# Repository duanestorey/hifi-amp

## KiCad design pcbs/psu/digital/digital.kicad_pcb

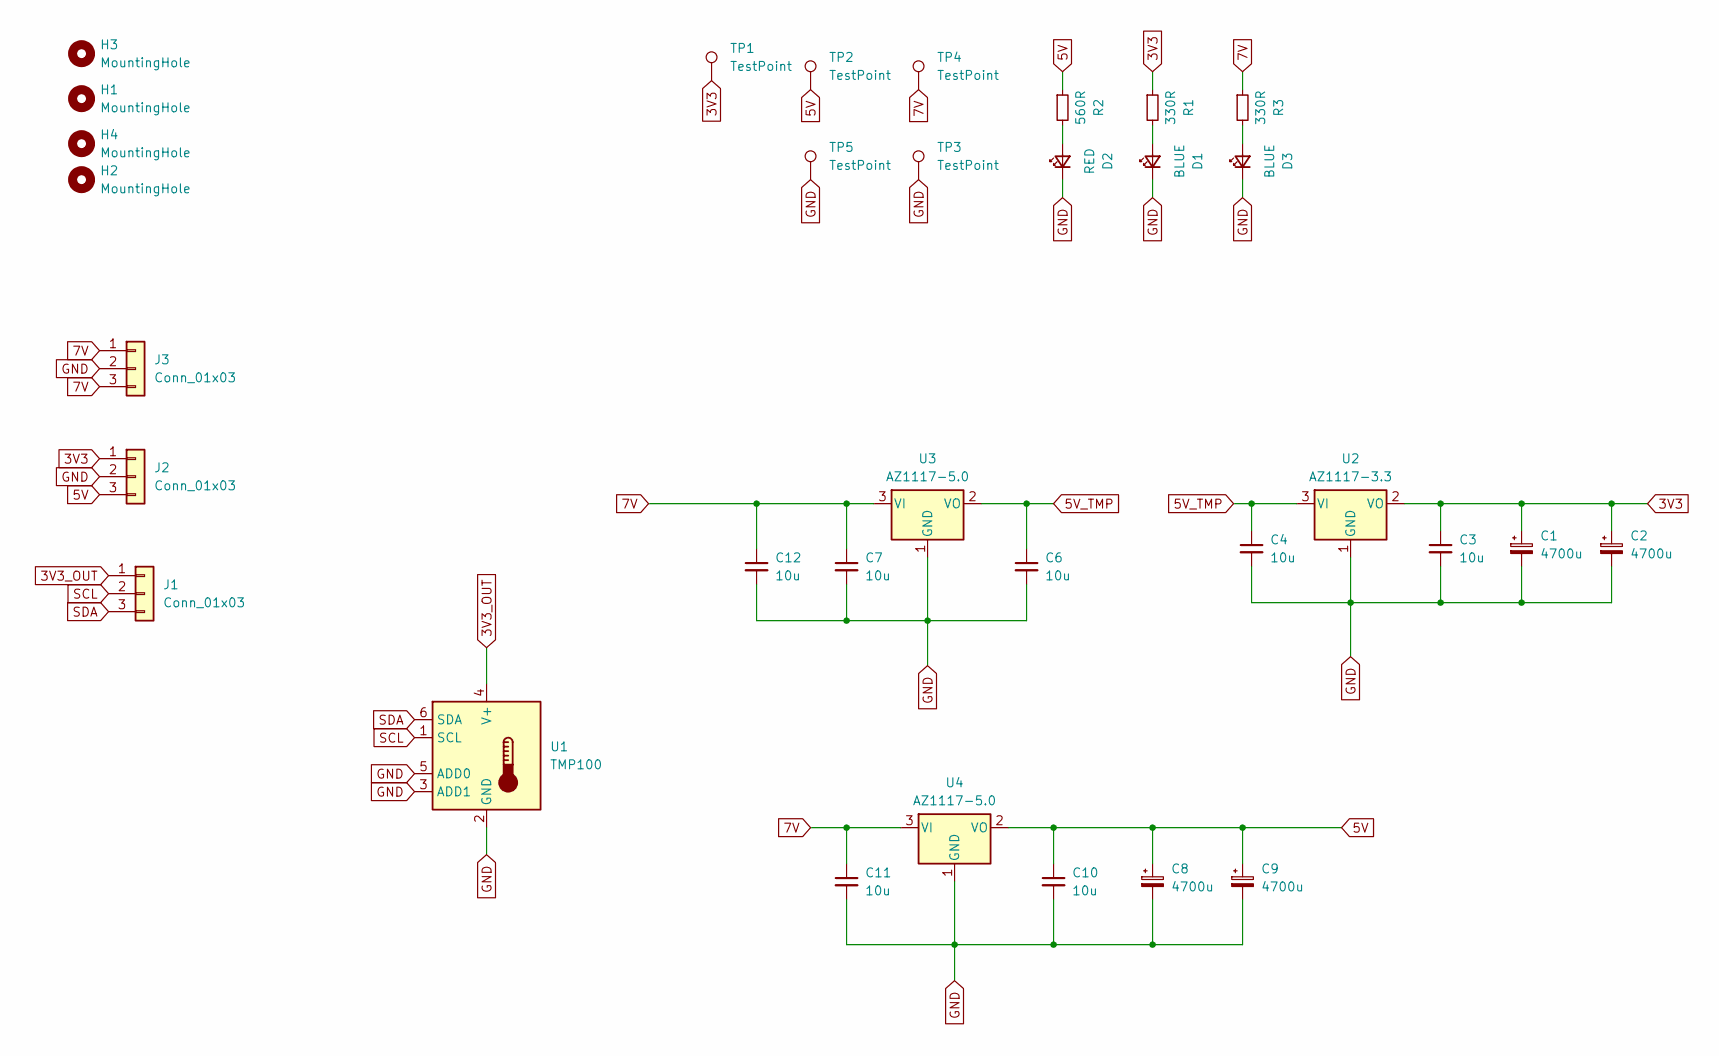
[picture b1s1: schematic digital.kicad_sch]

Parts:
C1, C2, C8, C9: 4700u; CP_Radial_D16.0mm_P7.50mm
C3, C4, C6, C7, C10, C11, C12: 10u; C_1206_3216Metric_Pad1.33x1.80mm_HandSolder
D1, D3: BLUE; LED_0805_2012Metric_Pad1.15x1.40mm_HandSolder
D2: RED; LED_0805_2012Metric_Pad1.15x1.40mm_HandSolder
H1, H2, H3, H4: MountingHole; MountingHole_3.2mm_M3_DIN965_Pad_TopBottom
J1: Conn_01x03; JST_PH_B3B-PH-K_1x03_P2.00mm_Vertical
J2, J3: Conn_01x03; JST_VH_B3P-VH-B_1x03_P3.96mm_Vertical
R1, R3: 330R; R_0805_2012Metric_Pad1.20x1.40mm_HandSolder
R2: 560R; R_0805_2012Metric_Pad1.20x1.40mm_HandSolder
TP1, TP2, TP3, TP4, TP5: TestPoint; TestPoint_THTPad_2.5x2.5mm_Drill1.2mm
U1: TMP100; SOT-23-6
U2: AZ1117-3.3; SOT-223
U3, U4: AZ1117-5.0; SOT-223

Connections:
3V3: C1.1, C2.1, C3.1, J2.1, R1.1, TP1.1, U2.2 (VO)
3V3_OUT: J1.1, U1.4 (V+)
5V: C8.1, C9.1, C10.1, J2.3, R2.1, TP2.1, U4.2 (VO)
5V_TMP: C4.1, C6.1, U2.3 (VI), U3.2 (VO)
7V: C7.1, C11.1, C12.1, J3.1, J3.3, R3.1, TP4.1, U3.3 (VI), U4.3 (VI)
GND: C1.2, C2.2, C3.2, C4.2, C6.2, C7.2, C8.2, C9.2, C10.2, C11.2, C12.2, D1.1 (K), D2.1 (K), D3.1 (K), J2.2, J3.2, TP3.1, TP5.1, U1.2 (GND), U1.3 (ADD1), U1.5 (ADD0), U2.1 (GND), U3.1 (GND), U4.1 (GND)
unnamed: D1.2 (A), R1.2
unnamed: D2.2 (A), R2.2
unnamed: D3.2 (A), R3.2
SCL: J1.2, U1.1 (SCL)
SDA: J1.3, U1.6 (SDA)

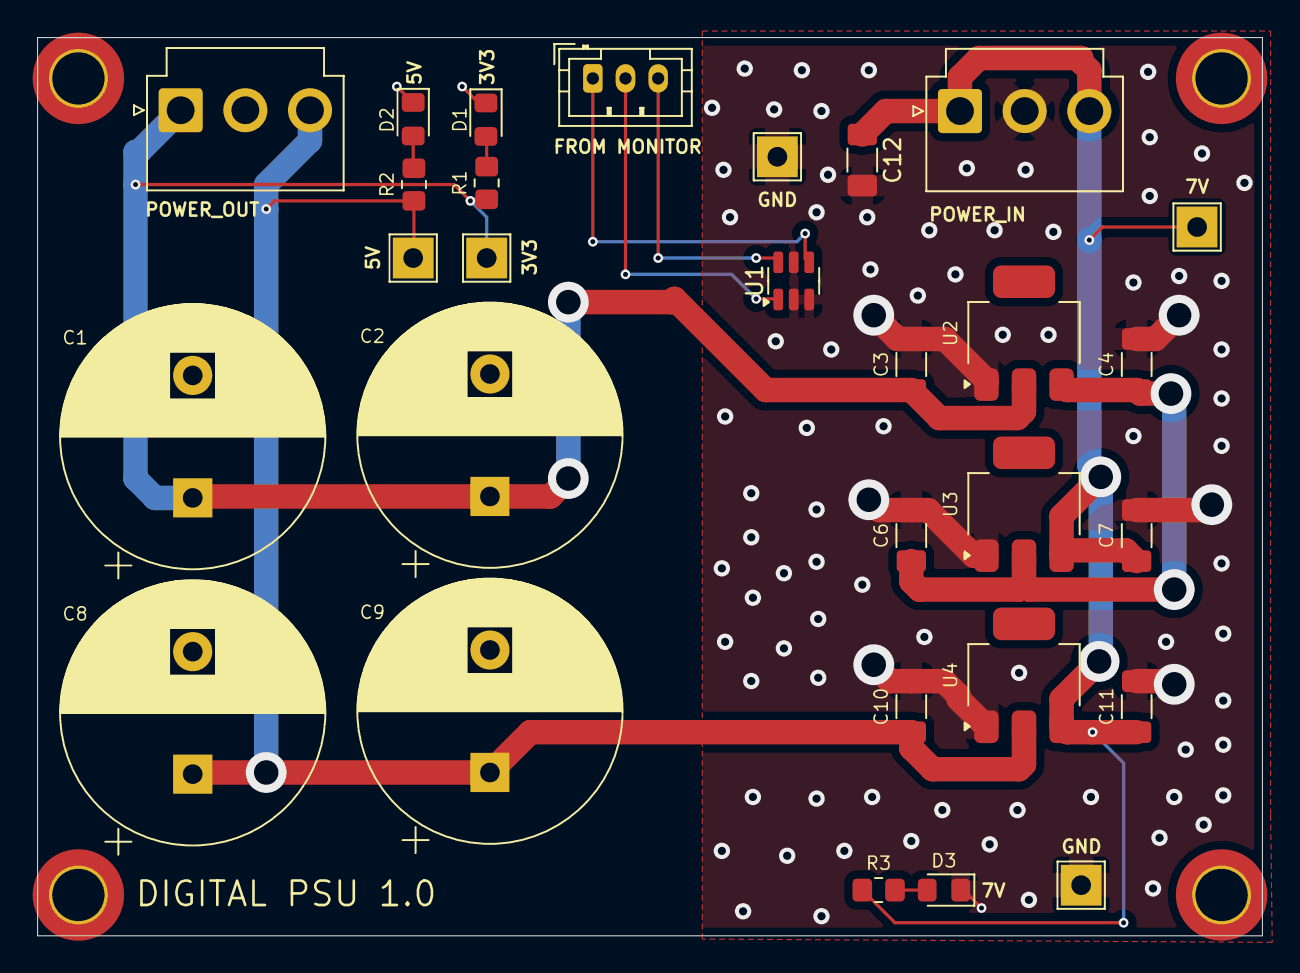
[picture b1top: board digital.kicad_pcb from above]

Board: 2 copper layers, 75.0 x 55.0 mm, 33 parts (0 on the bottom side), 11 nets.

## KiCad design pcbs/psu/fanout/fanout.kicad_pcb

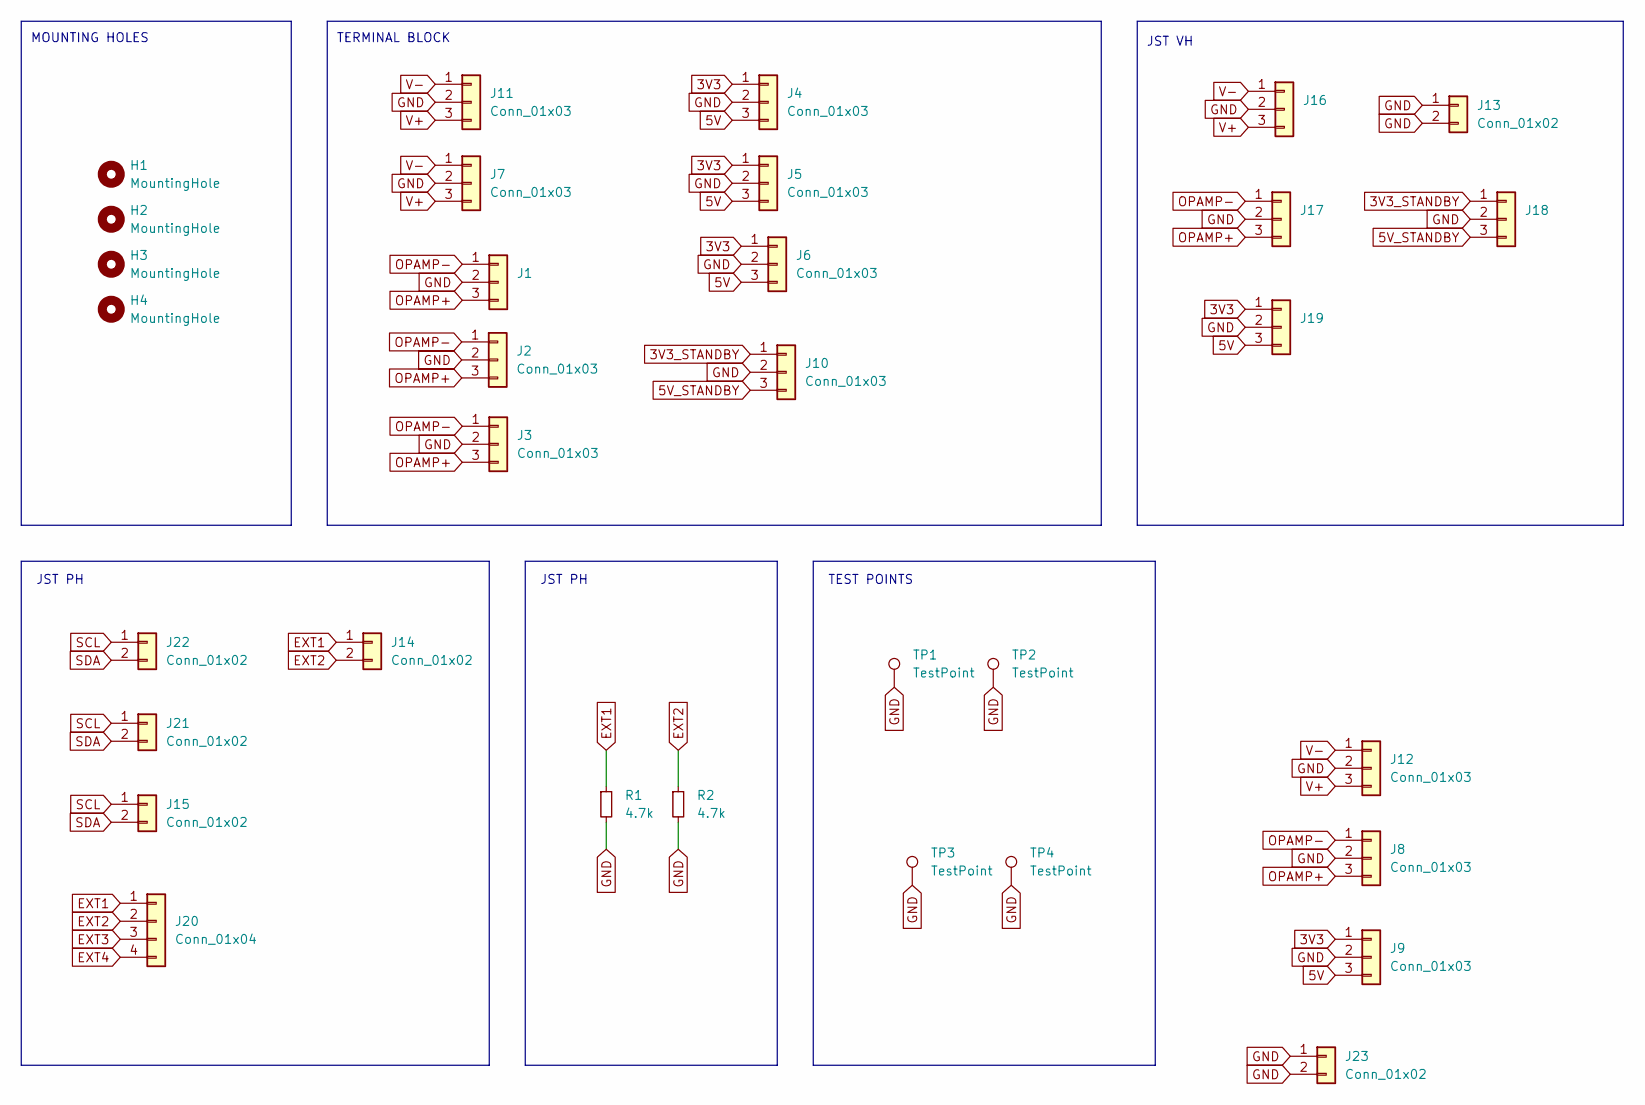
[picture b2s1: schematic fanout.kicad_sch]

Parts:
H1, H2, H3, H4: MountingHole; MountingHole_3.2mm_M3_DIN965_Pad_TopBottom
J1, J2, J3, J4, J5, J6, J7, J10, J11: Conn_01x03; TerminalBlock_Phoenix_PT-1,5-3-3.5-H_1x03_P3.50mm_Horizontal
J8, J9, J12: Conn_01x03; JST_PH_B3B-PH-K_1x03_P2.00mm_Vertical
J13: Conn_01x02; JST_VH_B2P-VH-B_1x02_P3.96mm_Vertical
J14, J15, J21, J22: Conn_01x02; JST_PH_B2B-PH-K_1x02_P2.00mm_Vertical
J16, J17, J18, J19: Conn_01x03; JST_VH_B3P-VH-B_1x03_P3.96mm_Vertical
J20: Conn_01x04; JST_PH_B4B-PH-K_1x04_P2.00mm_Vertical
J23: Conn_01x02; PinHeader_1x02_P2.54mm_Vertical
R1, R2: 4.7k; R_0805_2012Metric_Pad1.20x1.40mm_HandSolder
TP1, TP2, TP3, TP4: TestPoint; TestPoint_THTPad_2.5x2.5mm_Drill1.2mm

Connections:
3V3: J4.1, J5.1, J6.1, J9.1, J19.1
3V3_STANDBY: J10.1, J18.1
5V: J4.3, J5.3, J6.3, J9.3, J19.3
5V_STANDBY: J10.3, J18.3
EXT1: J14.1, J20.1, R1.1
EXT2: J14.2, J20.2, R2.1
EXT3: J20.3
EXT4: J20.4
GND: J1.2, J2.2, J3.2, J4.2, J5.2, J6.2, J7.2, J8.2, J9.2, J10.2, J11.2, J12.2, J13.1, J13.2, J16.2, J17.2, J18.2, J19.2, J23.1, J23.2, R1.2, R2.2, TP1.1, TP2.1, TP3.1, TP4.1
OPAMP+: J1.3, J2.3, J3.3, J8.3, J17.3
OPAMP-: J1.1, J2.1, J3.1, J8.1, J17.1
SCL: J15.1, J21.1, J22.1
SDA: J15.2, J21.2, J22.2
V+: J7.3, J11.3, J12.3, J16.3
V-: J7.1, J11.1, J12.1, J16.1

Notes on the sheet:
TEST POINTS
JST VH
MOUNTING HOLES
JST PH
TERMINAL BLOCK

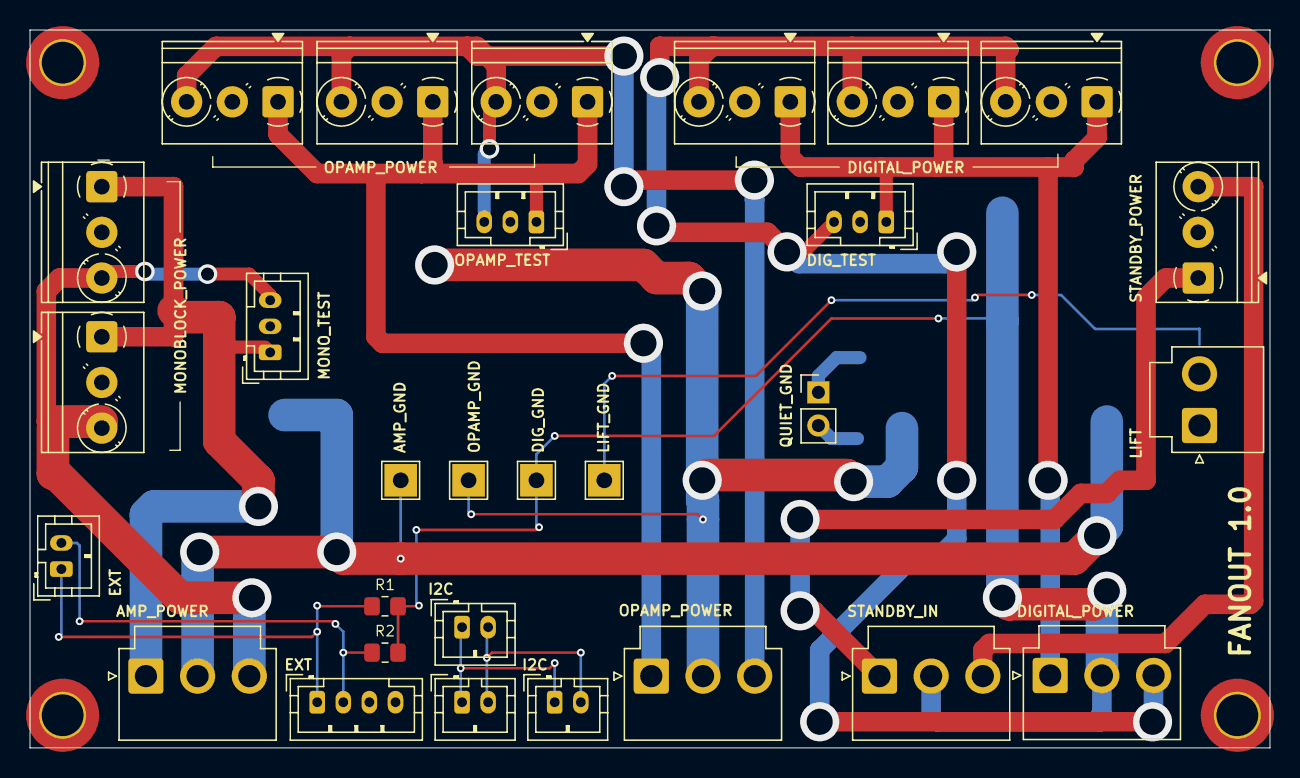
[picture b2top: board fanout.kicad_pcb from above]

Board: 2 copper layers, 95.0 x 55.0 mm, 33 parts (0 on the bottom side), 13 nets.

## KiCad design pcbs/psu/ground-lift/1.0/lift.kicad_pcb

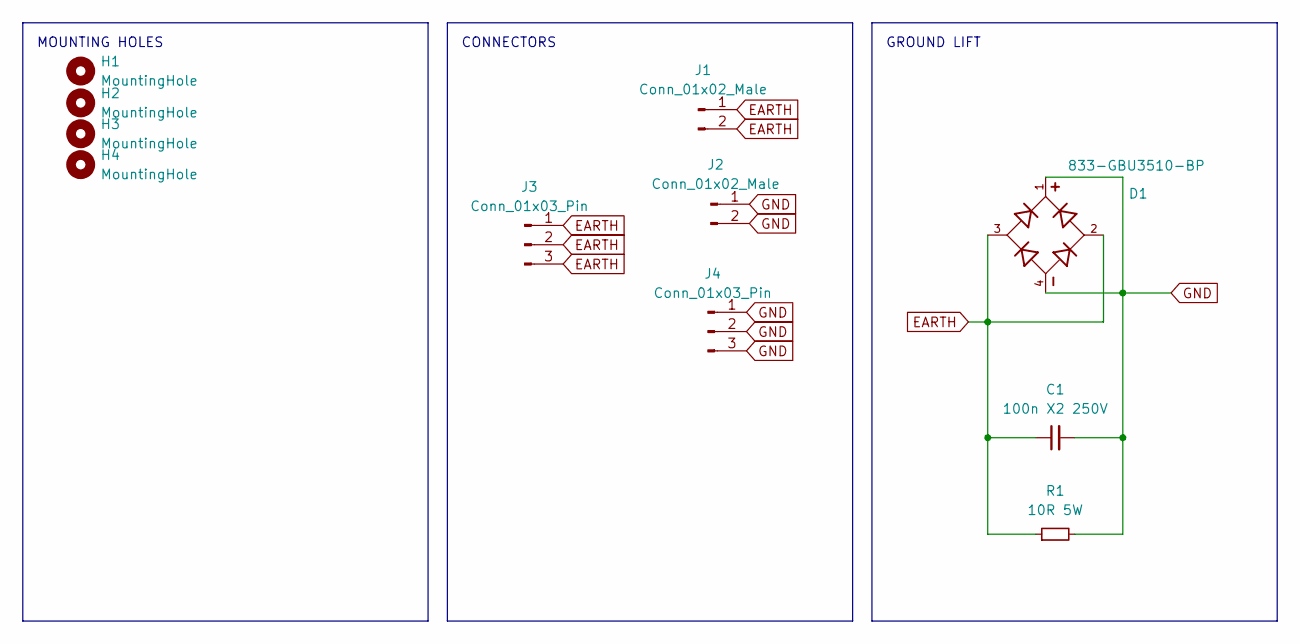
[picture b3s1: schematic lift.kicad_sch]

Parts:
C1: 100n X2 250V; C_Rect_L18.0mm_W5.0mm_P15.00mm_FKS3_FKP3; Mouser 871-B32922X2104K000
D1: 833-GBU3510-BP; Diode_Bridge_Vishay_GBU; Mouser 833-GBU3510-BP
H1, H2, H3, H4: MountingHole; MountingHole_3.2mm_M3_DIN965_Pad_TopOnly
J1, J2: Conn_01x02_Male; JST_VH_B2P-VH-B_1x02_P3.96mm_Vertical
J3, J4: Conn_01x03_Pin; TerminalBlock_Phoenix_PT-1,5-3-5.0-H_1x03_P5.00mm_Horizontal
R1: 10R 5W; R_Axial_DIN0617_L17.0mm_D6.0mm_P25.40mm_Horizontal; Mouser 594-AC05W10R00J

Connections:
EARTH: C1.1, D1.2, D1.3, J1.1, J1.2, J3.1, J3.2, J3.3, R1.1
GND: C1.2, D1.1, D1.4, J2.1, J2.2, J4.1, J4.2, J4.3, R1.2

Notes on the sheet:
CONNECTORS
GROUND LIFT
MOUNTING HOLES

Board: 2 copper layers, 11 parts (0 on the bottom side), 2 nets, no tracks yet.

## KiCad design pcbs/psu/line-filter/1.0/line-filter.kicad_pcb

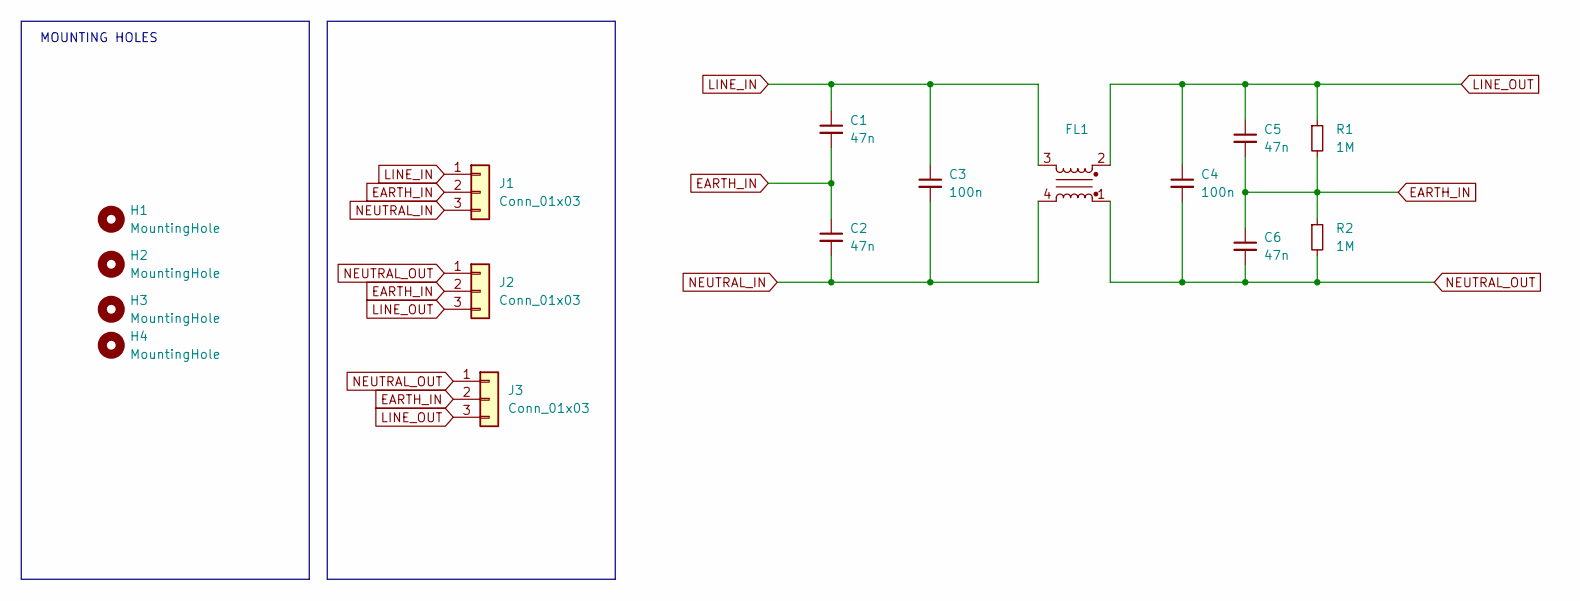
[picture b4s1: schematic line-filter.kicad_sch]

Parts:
C1, C2, C5, C6: 47n; C_Rect_L18.0mm_W7.0mm_P15.00mm_FKS3_FKP3
C3, C4: 100n; C_Rect_L18.0mm_W5.0mm_P15.00mm_FKS3_FKP3
FL1: Choke_CommonMode_PulseElectronics_PH9455x356NL; SSR21NV-M
H1, H2, H3, H4: MountingHole; MountingHole_3.2mm_M3_DIN965_Pad_TopBottom
J1, J2, J3: Conn_01x03; TerminalBlock_Phoenix_MKDS-1,5-3_1x03_P5.00mm_Horizontal
R1, R2: 1M; R_1206_3216Metric_Pad1.30x1.75mm_HandSolder

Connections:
EARTH_IN: C1.2, C2.1, C5.2, C6.1, J1.2, J2.2, J3.2, R1.2, R2.1
LINE_IN: C1.1, C3.1, FL1.3, J1.1
LINE_OUT: C4.1, C5.1, FL1.2, J2.3, J3.3, R1.1
NEUTRAL_IN: C2.2, C3.2, FL1.4, J1.3
NEUTRAL_OUT: C4.2, C6.2, FL1.1, J2.1, J3.1, R2.2

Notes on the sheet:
MOUNTING HOLES

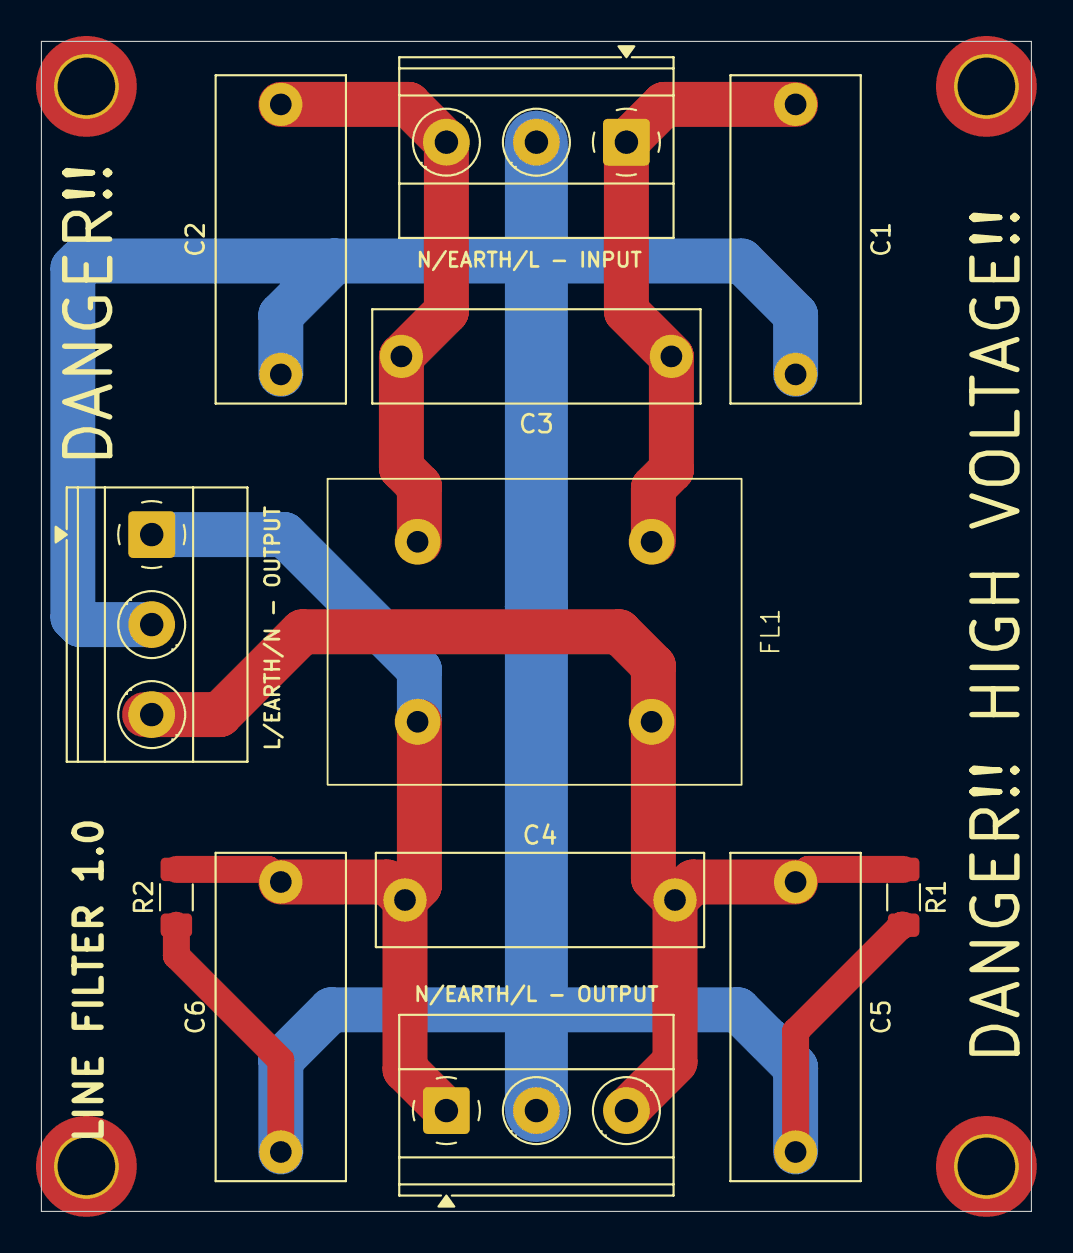
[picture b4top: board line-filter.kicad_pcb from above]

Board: 2 copper layers, 55.0 x 65.0 mm, 16 parts (0 on the bottom side), 5 nets.

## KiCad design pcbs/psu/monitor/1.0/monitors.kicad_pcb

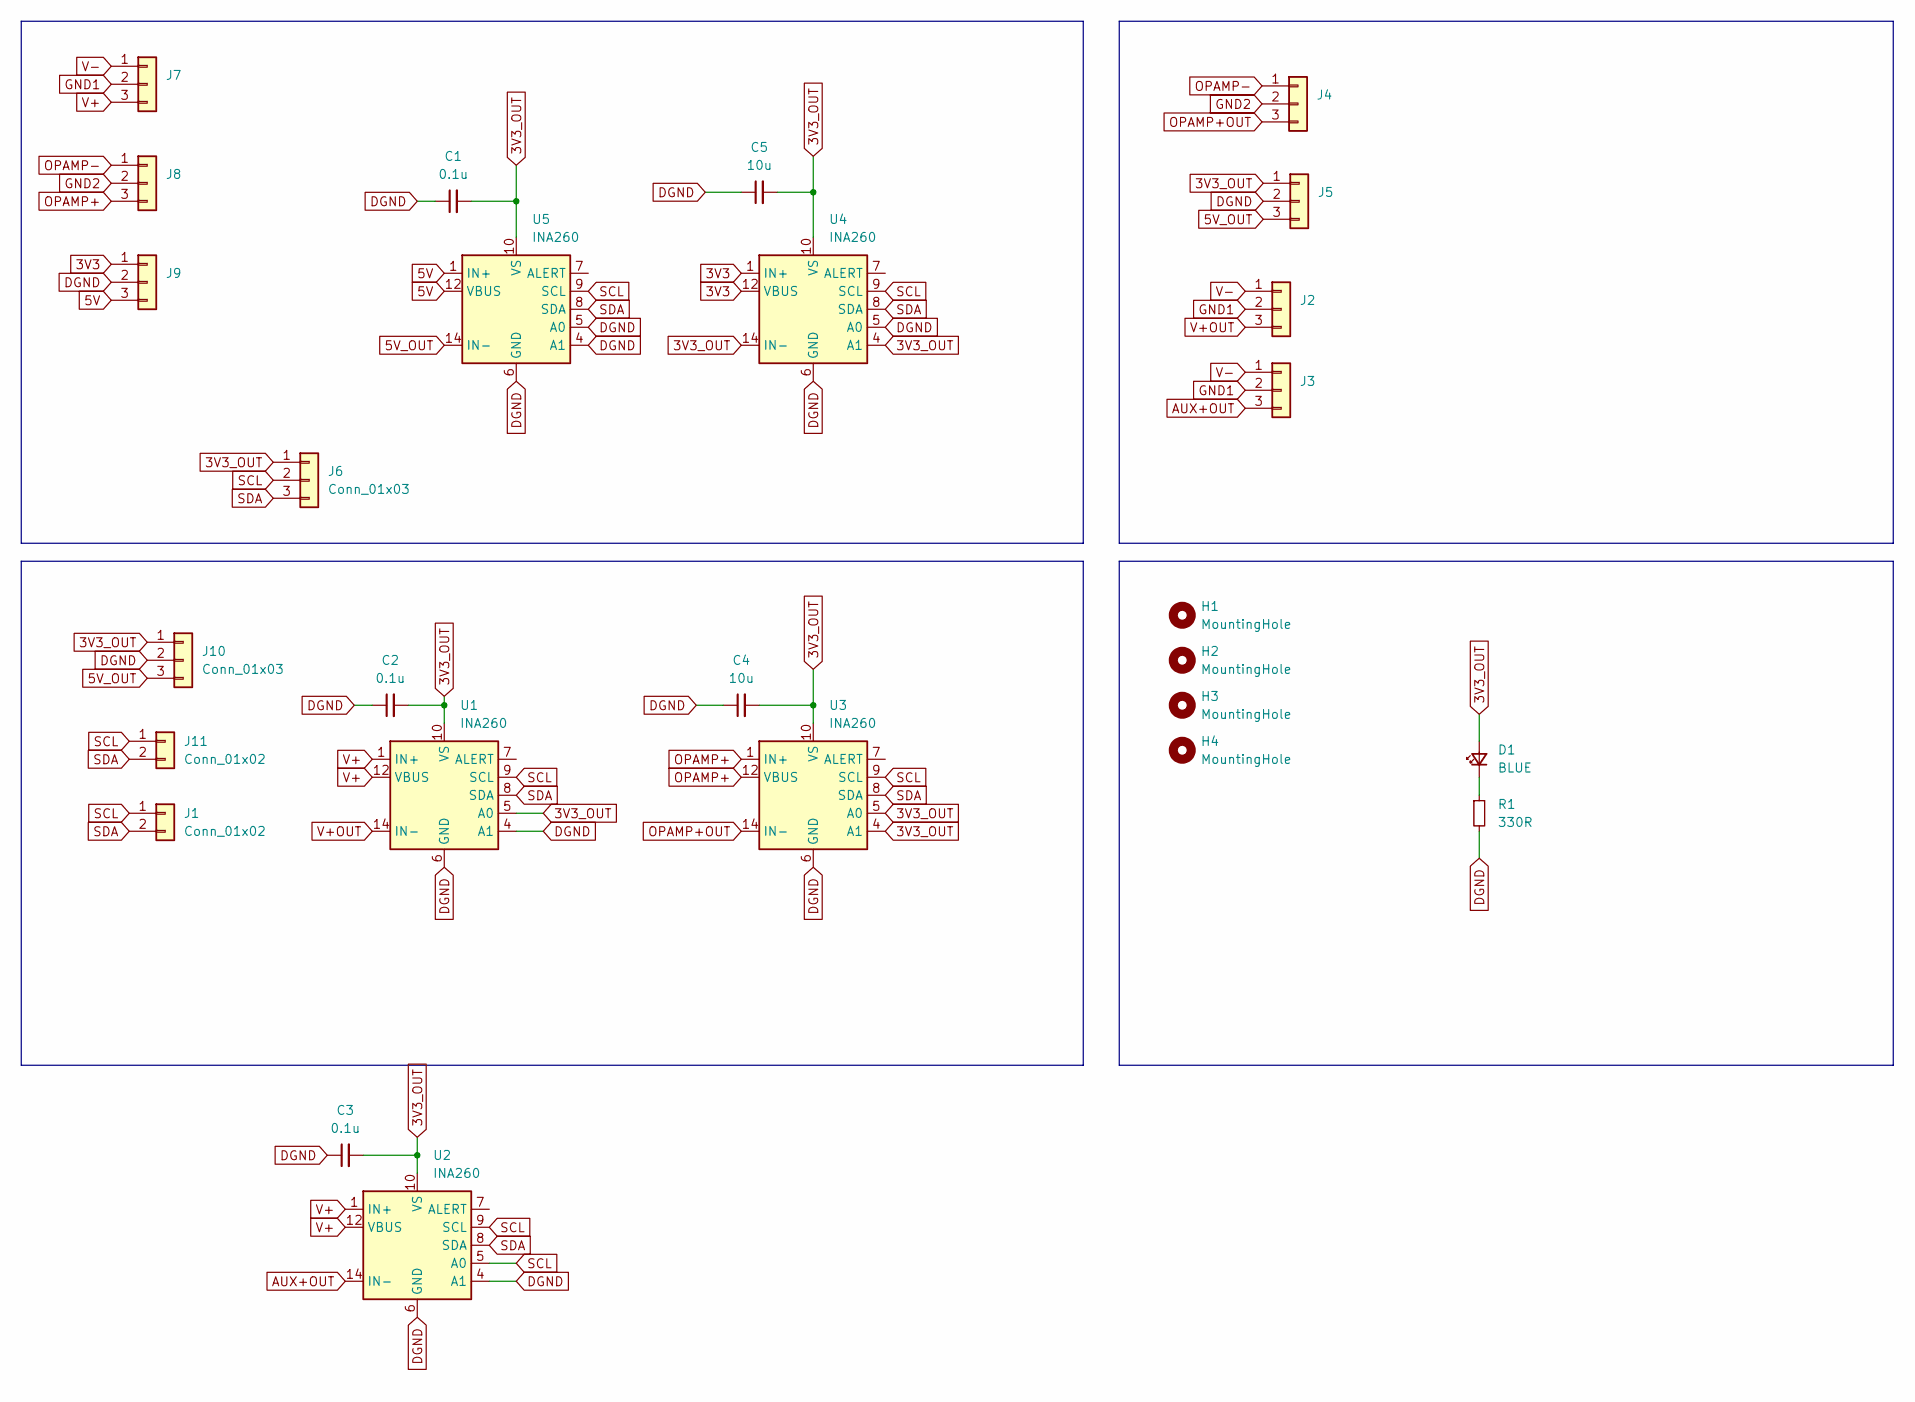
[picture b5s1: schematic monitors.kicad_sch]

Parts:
C1, C2, C3: 0.1u; C_0805_2012Metric_Pad1.18x1.45mm_HandSolder
C4, C5: 10u; C_1206_3216Metric_Pad1.33x1.80mm_HandSolder
D1: BLUE; LED_0805_2012Metric_Pad1.15x1.40mm_HandSolder
H1, H2, H3, H4: MountingHole; MountingHole_3.2mm_M3_DIN965_Pad_TopBottom
J1, J11: Conn_01x02; JST_PH_B2B-PH-K_1x02_P2.00mm_Vertical
J2, J3, J4, J5, J7, J8, J9: Conn_01x03; JST_VH_B3P-VH-B_1x03_P3.96mm_Vertical
J6, J10: Conn_01x03; JST_PH_B3B-PH-K_1x03_P2.00mm_Vertical
R1: 330R; R_0805_2012Metric_Pad1.20x1.40mm_HandSolder
U1, U2, U3, U4, U5: INA260; TSSOP-16_4.4x5mm_P0.65mm

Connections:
3V3: J9.1, U4.1 (IN+), U4.2 (IN+), U4.3 (IN+), U4.12 (VBUS)
3V3_OUT: C1.2, C2.2, C3.2, C4.2, C5.2, D1.2 (A), J5.1, J6.1, J10.1, U1.5 (A0), U1.10 (VS), U2.10 (VS), U3.4 (A1), U3.5 (A0), U3.10 (VS), U4.4 (A1), U4.10 (VS), U4.14 (IN-), U4.15 (IN-), U4.16 (IN-), U5.10 (VS)
5V: J9.3, U5.1 (IN+), U5.2 (IN+), U5.3 (IN+), U5.12 (VBUS)
5V_OUT: J5.3, J10.3, U5.14 (IN-), U5.15 (IN-), U5.16 (IN-)
AUX+OUT: J3.3, U2.14 (IN-), U2.15 (IN-), U2.16 (IN-)
DGND: C1.1, C2.1, C3.1, C4.1, C5.1, J5.2, J9.2, J10.2, R1.2, U1.4 (A1), U1.6 (GND), U1.11 (GND), U2.4 (A1), U2.6 (GND), U2.11 (GND), U3.6 (GND), U3.11 (GND), U4.5 (A0), U4.6 (GND), U4.11 (GND), U5.4 (A1), U5.5 (A0), U5.6 (GND), U5.11 (GND)
GND1: J2.2, J3.2, J7.2
GND2: J4.2, J8.2
unnamed: D1.1 (K), R1.1
OPAMP+: J8.3, U3.1 (IN+), U3.2 (IN+), U3.3 (IN+), U3.12 (VBUS)
OPAMP+OUT: J4.3, U3.14 (IN-), U3.15 (IN-), U3.16 (IN-)
OPAMP-: J4.1, J8.1
SCL: J1.1, J6.2, J11.1, U1.9 (SCL), U2.5 (A0), U2.9 (SCL), U3.9 (SCL), U4.9 (SCL), U5.9 (SCL)
SDA: J1.2, J6.3, J11.2, U1.8 (SDA), U2.8 (SDA), U3.8 (SDA), U4.8 (SDA), U5.8 (SDA)
V+: J7.3, U1.1 (IN+), U1.2 (IN+), U1.3 (IN+), U1.12 (VBUS), U2.1 (IN+), U2.2 (IN+), U2.3 (IN+), U2.12 (VBUS)
V+OUT: J2.3, U1.14 (IN-), U1.15 (IN-), U1.16 (IN-)
V-: J2.1, J3.1, J7.1

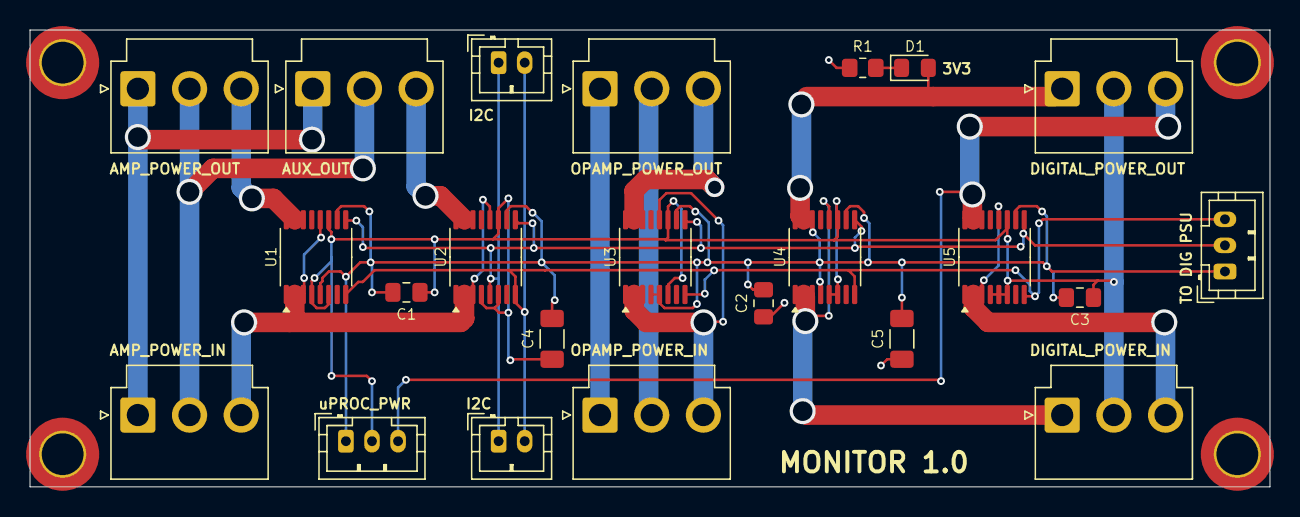
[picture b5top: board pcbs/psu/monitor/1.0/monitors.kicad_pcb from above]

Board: 2 copper layers, 95.0 x 35.0 mm, 27 parts (0 on the bottom side), 17 nets.

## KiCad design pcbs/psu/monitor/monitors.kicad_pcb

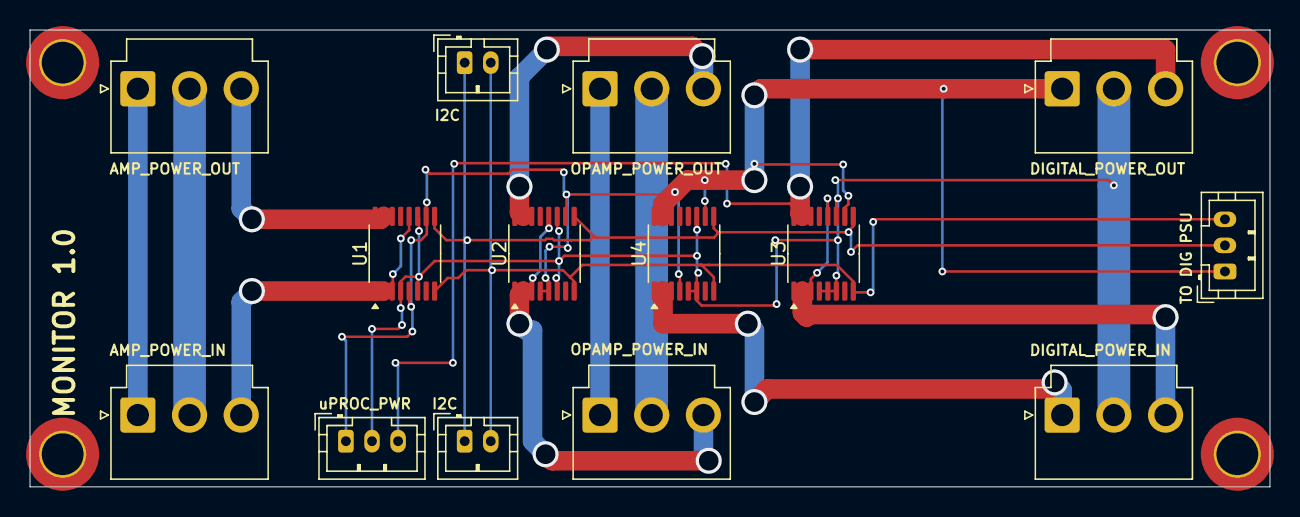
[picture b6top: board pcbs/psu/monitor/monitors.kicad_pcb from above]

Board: 2 copper layers, 95.0 x 35.0 mm, 18 parts (0 on the bottom side), 13 nets.

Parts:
H1, H2, H3, H4: MountingHole; MountingHole_3.2mm_M3_DIN965_Pad_TopBottom
J6, J7, J8, J9, J10, J11: Conn_01x03; JST_VH_B3P-VH-B_1x03_P3.96mm_Vertical
J13, J15: Conn_01x03; JST_PH_B3B-PH-K_1x03_P2.00mm_Vertical
J16, J17: Conn_01x02; JST_PH_B2B-PH-K_1x02_P2.00mm_Vertical
U1, U2, U3, U4: INA260; TSSOP-16_4.4x5mm_P0.65mm

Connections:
3V3: J8.1, U4.1 (IN+), U4.2 (IN+), U4.3 (IN+)
3V3_OUT: J10.1, J13.1, J15.1, U1.5 (A0), U1.10 (VS), U2.4 (A1), U2.5 (A0), U2.10 (VS), U3.10 (VS), U4.4 (A1), U4.10 (VS), U4.14 (IN-), U4.15 (IN-), U4.16 (IN-)
5V: J8.3, U3.1 (IN+), U3.2 (IN+), U3.3 (IN+), U3.12 (VBUS)
5V_OUT: J10.3, J13.3, U3.14 (IN-), U3.15 (IN-), U3.16 (IN-)
GND: J6.2, J7.2, J8.2, J9.2, J10.2, J11.2, J13.2, U1.4 (A1), U1.6 (GND), U1.11 (GND), U2.6 (GND), U2.11 (GND), U3.4 (A1), U3.5 (A0), U3.6 (GND), U3.11 (GND), U4.5 (A0), U4.6 (GND), U4.11 (GND)
OPAMP+: J7.3, U2.1 (IN+), U2.2 (IN+), U2.3 (IN+), U2.12 (VBUS)
OPAMP+OUT: J9.3, U2.14 (IN-), U2.15 (IN-), U2.16 (IN-)
OPAMP-: J7.1, J9.1
SCL: J15.2, J16.1, J17.1, U1.9 (SCL), U2.9 (SCL), U3.9 (SCL), U4.9 (SCL)
SDA: J15.3, J16.2, J17.2, U1.8 (SDA), U2.8 (SDA), U3.8 (SDA), U4.8 (SDA)
V+: J6.3, U1.1 (IN+), U1.2 (IN+), U1.3 (IN+), U1.12 (VBUS)
V+OUT: J11.3, U1.14 (IN-), U1.15 (IN-), U1.16 (IN-)
V-: J6.1, J11.1
